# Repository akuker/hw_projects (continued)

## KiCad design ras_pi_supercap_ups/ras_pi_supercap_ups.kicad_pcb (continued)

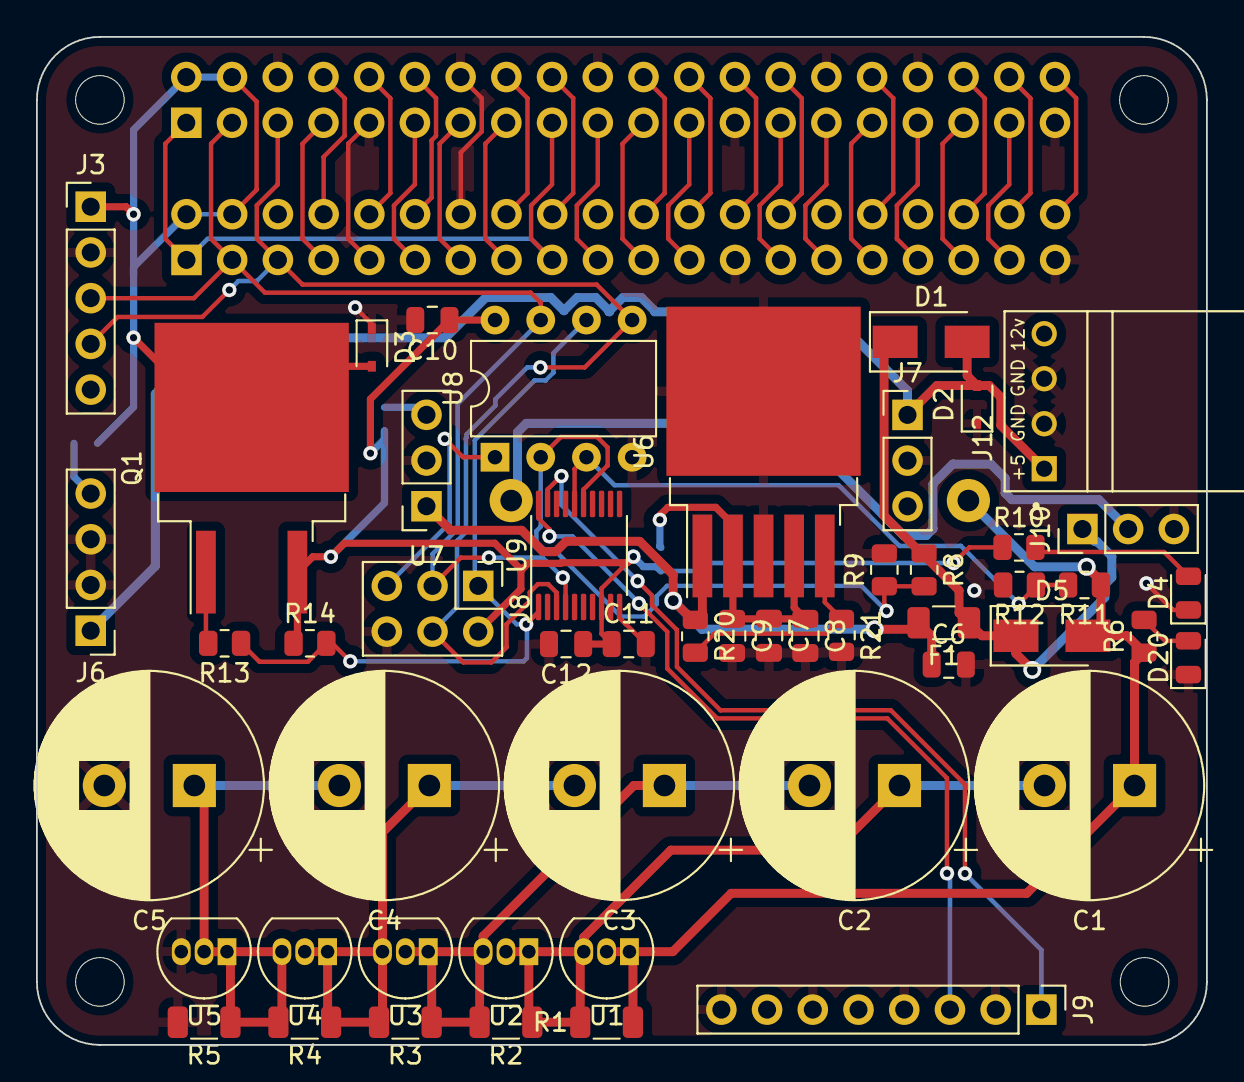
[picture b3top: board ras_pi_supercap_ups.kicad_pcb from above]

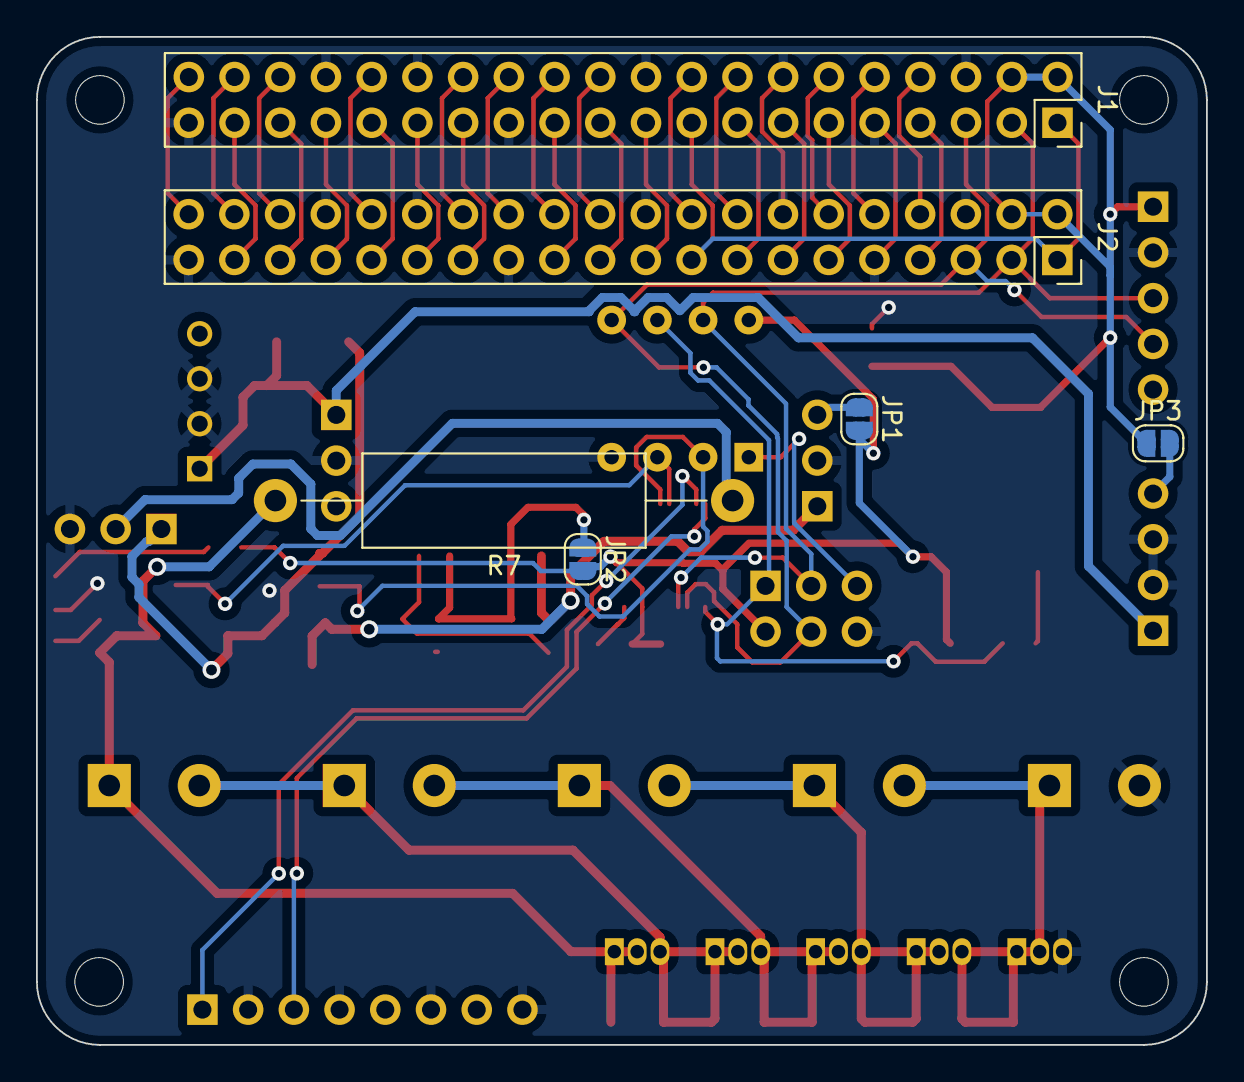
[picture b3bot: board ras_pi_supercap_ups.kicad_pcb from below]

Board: 2 copper layers, 65.0 x 56.0 mm, 61 parts (6 on the bottom side), 54 nets.

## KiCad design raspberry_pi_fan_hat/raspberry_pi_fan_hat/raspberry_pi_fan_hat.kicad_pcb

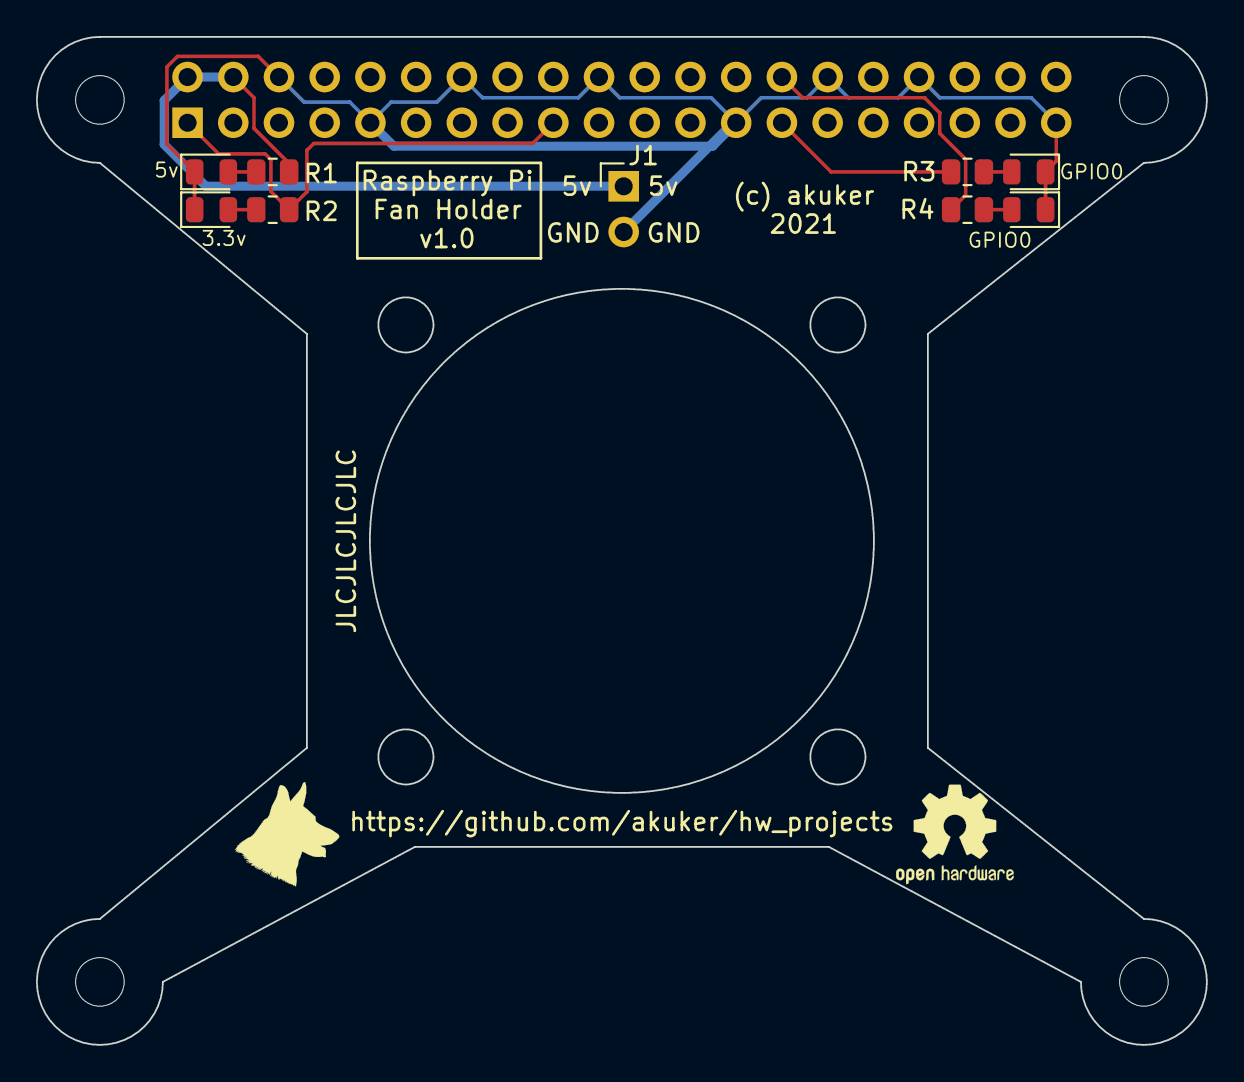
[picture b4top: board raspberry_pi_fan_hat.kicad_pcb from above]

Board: 2 copper layers, 65.0 x 56.0 mm, 14 parts (1 on the bottom side), 9 nets.

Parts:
D1, D2, D3, D4: LED_Small; LED_0805_2012Metric
J1: Conn_01x02; PinHeader_1x02_P2.54mm_Horizontal
MK1, MK2, MK3, MK4: M2.5; MountingHole_2.7mm_M2.5
P1: Conn_02x20_Odd_Even; PinSocket_2x20_P2.54mm_Vertical
R1, R2, R3, R4: R_Small; R_0805_2012Metric

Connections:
+3V3: P1.1, P1.17, R2.1
+5V: J1.1, P1.2, P1.4, R1.1
/ID_SC: P1.28, R4.1
/ID_SD: P1.27, R3.1
GND: D1.1, D2.1, D3.1, D4.1, J1.2, P1.6, P1.9, P1.14, P1.20, P1.25, P1.30, P1.34, P1.39
unnamed: D1.2, R1.2
unnamed: D2.2, R2.2
unnamed: D3.2, R3.2
unnamed: D4.2, R4.2

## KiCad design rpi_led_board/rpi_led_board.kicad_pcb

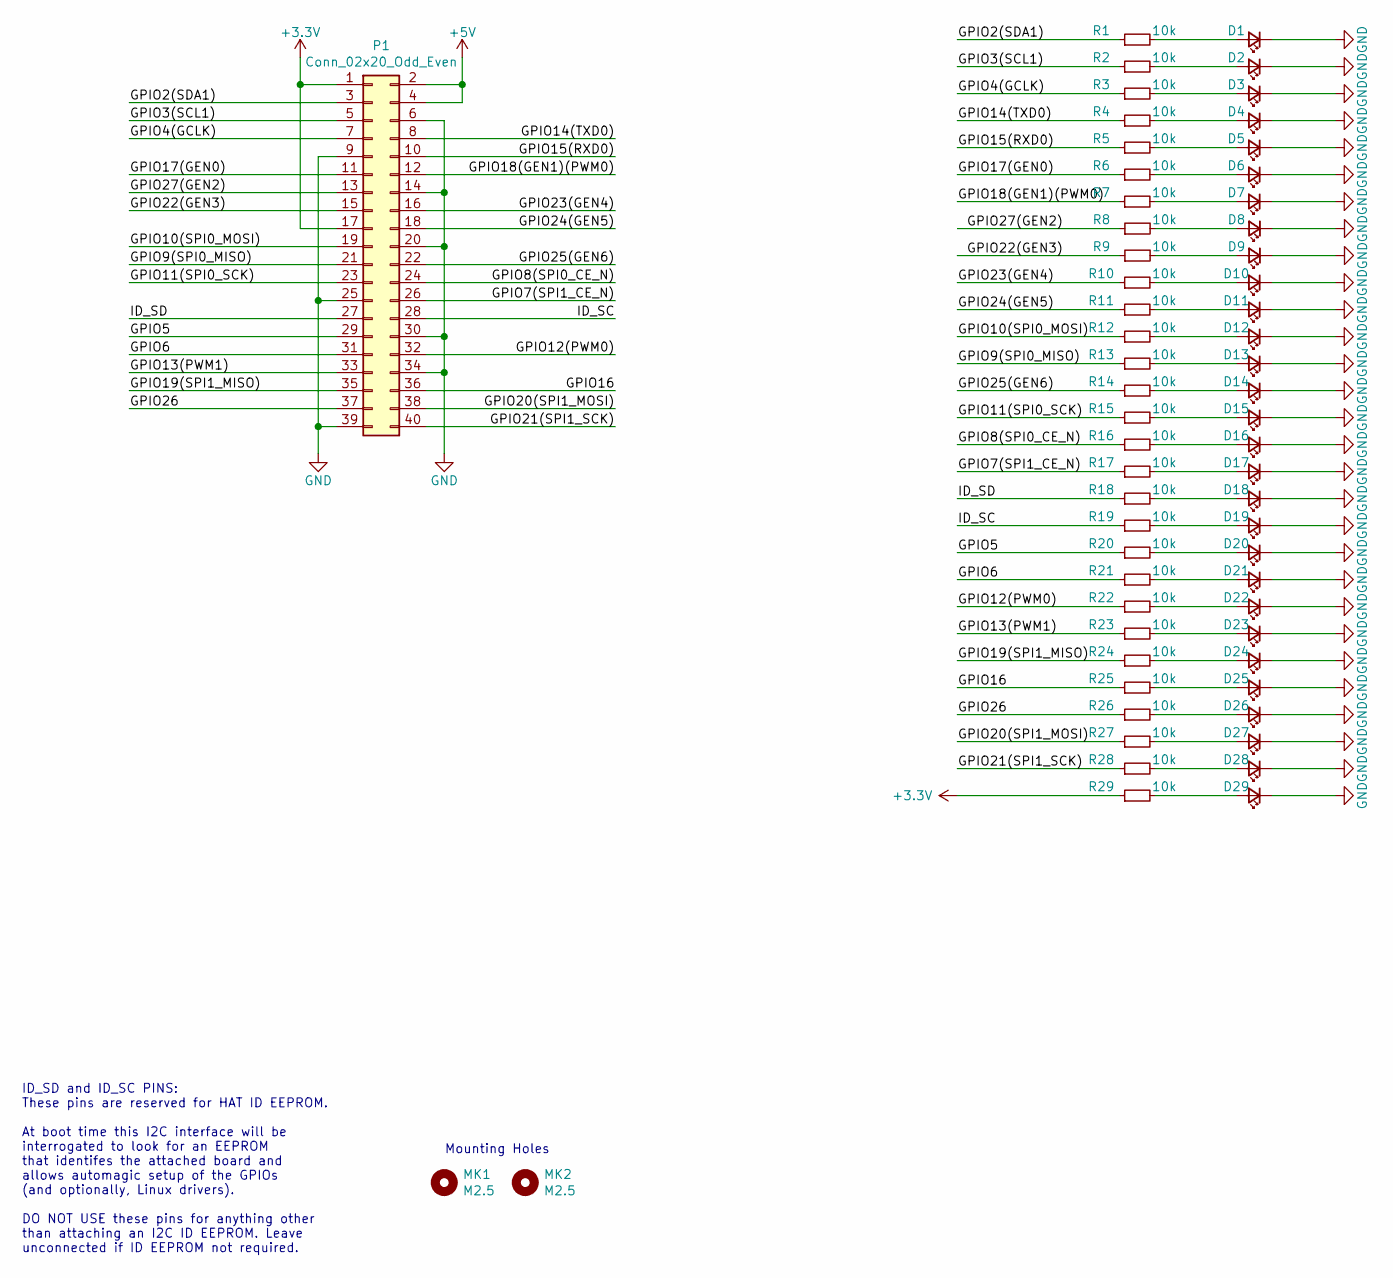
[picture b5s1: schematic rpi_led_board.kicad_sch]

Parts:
D1, D2, D3, D4, D5, D6, D7, D8, D9, D10, D11, D12, D13, D14, D15, D16, D17, D18, D19, D20, D21, D22, D23, D24, D25, D26, D27, D28, D29: Yellow; LED_0805_2012Metric; LCSC C2296
MK1, MK2: M2.5; MountingHole_2.7mm_M2.5
P1: Conn_02x20_Odd_Even; PinSocket_2x20_P2.54mm_Vertical
R1, R2, R3, R4, R5, R6, R7, R8, R9, R10, R11, R12, R13, R14, R15, R16, R17, R18, R19, R20, R21, R22, R23, R24, R25, R26, R27, R28, R29: 10k; R_0805_2012Metric; LCSC C17724

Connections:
+3V3: P1.1, P1.17, R29.1
+5V: P1.2, P1.4
/GPIO2(SDA1): P1.3, R1.1
/GPIO3(SCL1): P1.5, R2.1
/GPIO4(GCLK): P1.7, R3.1
/GPIO5: P1.29, R20.1
/GPIO6: P1.31, R21.1
/GPIO7(SPI1_CE_N): P1.26, R17.1
/GPIO8(SPI0_CE_N): P1.24, R16.1
/GPIO9(SPI0_MISO): P1.21, R13.1
/GPIO10(SPI0_MOSI): P1.19, R12.1
/GPIO11(SPI0_SCK): P1.23, R15.1
/GPIO12(PWM0): P1.32, R22.1
/GPIO13(PWM1): P1.33, R23.1
/GPIO14(TXD0): P1.8, R4.1
/GPIO15(RXD0): P1.10, R5.1
/GPIO16: P1.36, R25.1
/GPIO17(GEN0): P1.11, R6.1
/GPIO18(GEN1)(PWM0): P1.12, R7.1
/GPIO19(SPI1_MISO): P1.35, R24.1
/GPIO20(SPI1_MOSI): P1.38, R27.1
/GPIO21(SPI1_SCK): P1.40, R28.1
/GPIO22(GEN3): P1.15, R9.1
/GPIO23(GEN4): P1.16, R10.1
/GPIO24(GEN5): P1.18, R11.1
/GPIO25(GEN6): P1.22, R14.1
/GPIO26: P1.37, R26.1
/GPIO27(GEN2): P1.13, R8.1
/ID_SC: P1.28, R19.1
/ID_SD: P1.27, R18.1
GND: D1.1 (K), D2.1 (K), D3.1 (K), D4.1 (K), D5.1 (K), D6.1 (K), D7.1 (K), D8.1 (K), D9.1 (K), D10.1 (K), D11.1 (K), D12.1 (K), D13.1 (K), D14.1 (K), D15.1 (K), D16.1 (K), D17.1 (K), D18.1 (K), D19.1 (K), D20.1 (K), D21.1 (K), D22.1 (K), D23.1 (K), D24.1 (K), D25.1 (K), D26.1 (K), D27.1 (K), D28.1 (K), D29.1 (K), P1.6, P1.9, P1.14, P1.20, P1.25, P1.30, P1.34, P1.39
unnamed: D1.2 (A), R1.2
unnamed: D2.2 (A), R2.2
unnamed: D3.2 (A), R3.2
unnamed: D4.2 (A), R4.2
unnamed: D5.2 (A), R5.2
unnamed: D6.2 (A), R6.2
unnamed: D7.2 (A), R7.2
unnamed: D8.2 (A), R8.2
unnamed: D9.2 (A), R9.2
unnamed: D10.2 (A), R10.2
unnamed: D11.2 (A), R11.2
unnamed: D12.2 (A), R12.2
unnamed: D13.2 (A), R13.2
unnamed: D14.2 (A), R14.2
unnamed: D15.2 (A), R15.2
unnamed: D16.2 (A), R16.2
unnamed: D17.2 (A), R17.2
unnamed: D18.2 (A), R18.2
unnamed: D19.2 (A), R19.2
unnamed: D20.2 (A), R20.2
unnamed: D21.2 (A), R21.2
unnamed: D22.2 (A), R22.2
unnamed: D23.2 (A), R23.2
unnamed: D24.2 (A), R24.2
unnamed: D25.2 (A), R25.2
unnamed: D26.2 (A), R26.2
unnamed: D27.2 (A), R27.2
unnamed: D28.2 (A), R28.2
unnamed: D29.2 (A), R29.2

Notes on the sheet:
ID_SD and ID_SC PINS: These pins are reserved for HAT ID EEPROM. At boot time this I2C interface will be interrogated to look for an EEPROM that identifes the attached board and allows automagic setup of the GPIOs (and optionally, Linux drivers). DO NOT USE these pins for anything other than attach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
Mounting Holes

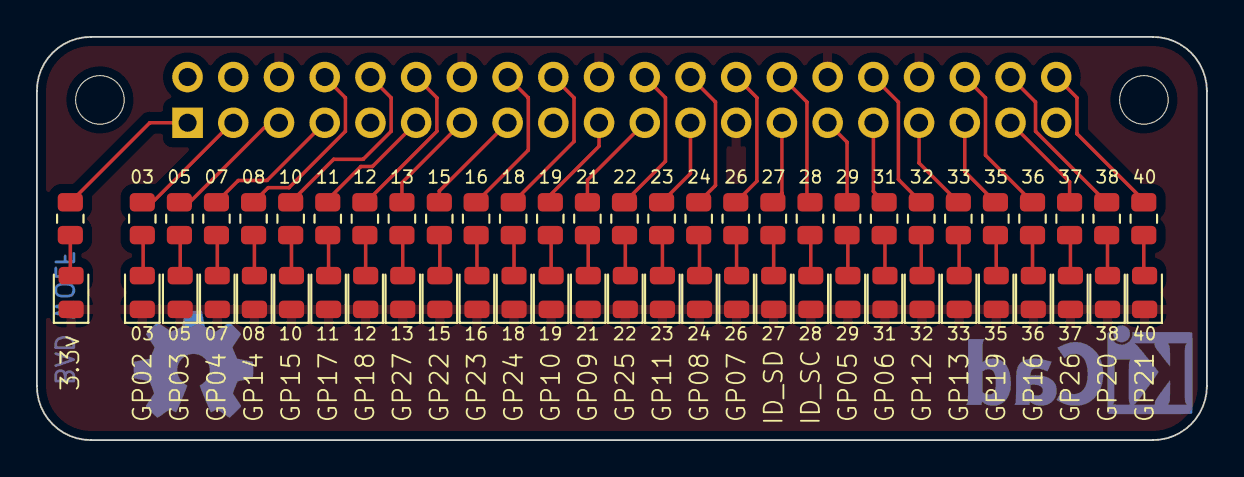
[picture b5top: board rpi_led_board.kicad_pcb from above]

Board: 2 copper layers, 65.0 x 22.4 mm, 61 parts (1 on the bottom side), 60 nets.

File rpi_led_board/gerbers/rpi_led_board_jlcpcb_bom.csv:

Comment,Designator,Footprint,LCSC
"Yellow","D1,D2,D3,D4,D5,D6,D7,D8,D9,D10,D11,D12,D13,D14,D15,D16,D17,D18,D19,D20,D21,D22,D23,D24,D25,D26,D27,D28,D29","LED_SMD:LED_0805_2012Metric","C2296"
"M2.5","MK1,MK2","MountingHole:MountingHole_2.7mm_M2.5",""
"Conn_02x20_Odd_Even","P1","Connector_PinSocket_2.54mm:PinSocket_2x20_P2.54mm_Vertical",""
"10k","R1,R2,R3,R4,R5,R6,R7,R8,R9,R10,R11,R12,R13,R14,R15,R16,R17,R18,R19,R20,R21,R22,R23,R24,R25,R26,R27,R28,R29","Resistor_SMD:R_0805_2012Metric","C17724"

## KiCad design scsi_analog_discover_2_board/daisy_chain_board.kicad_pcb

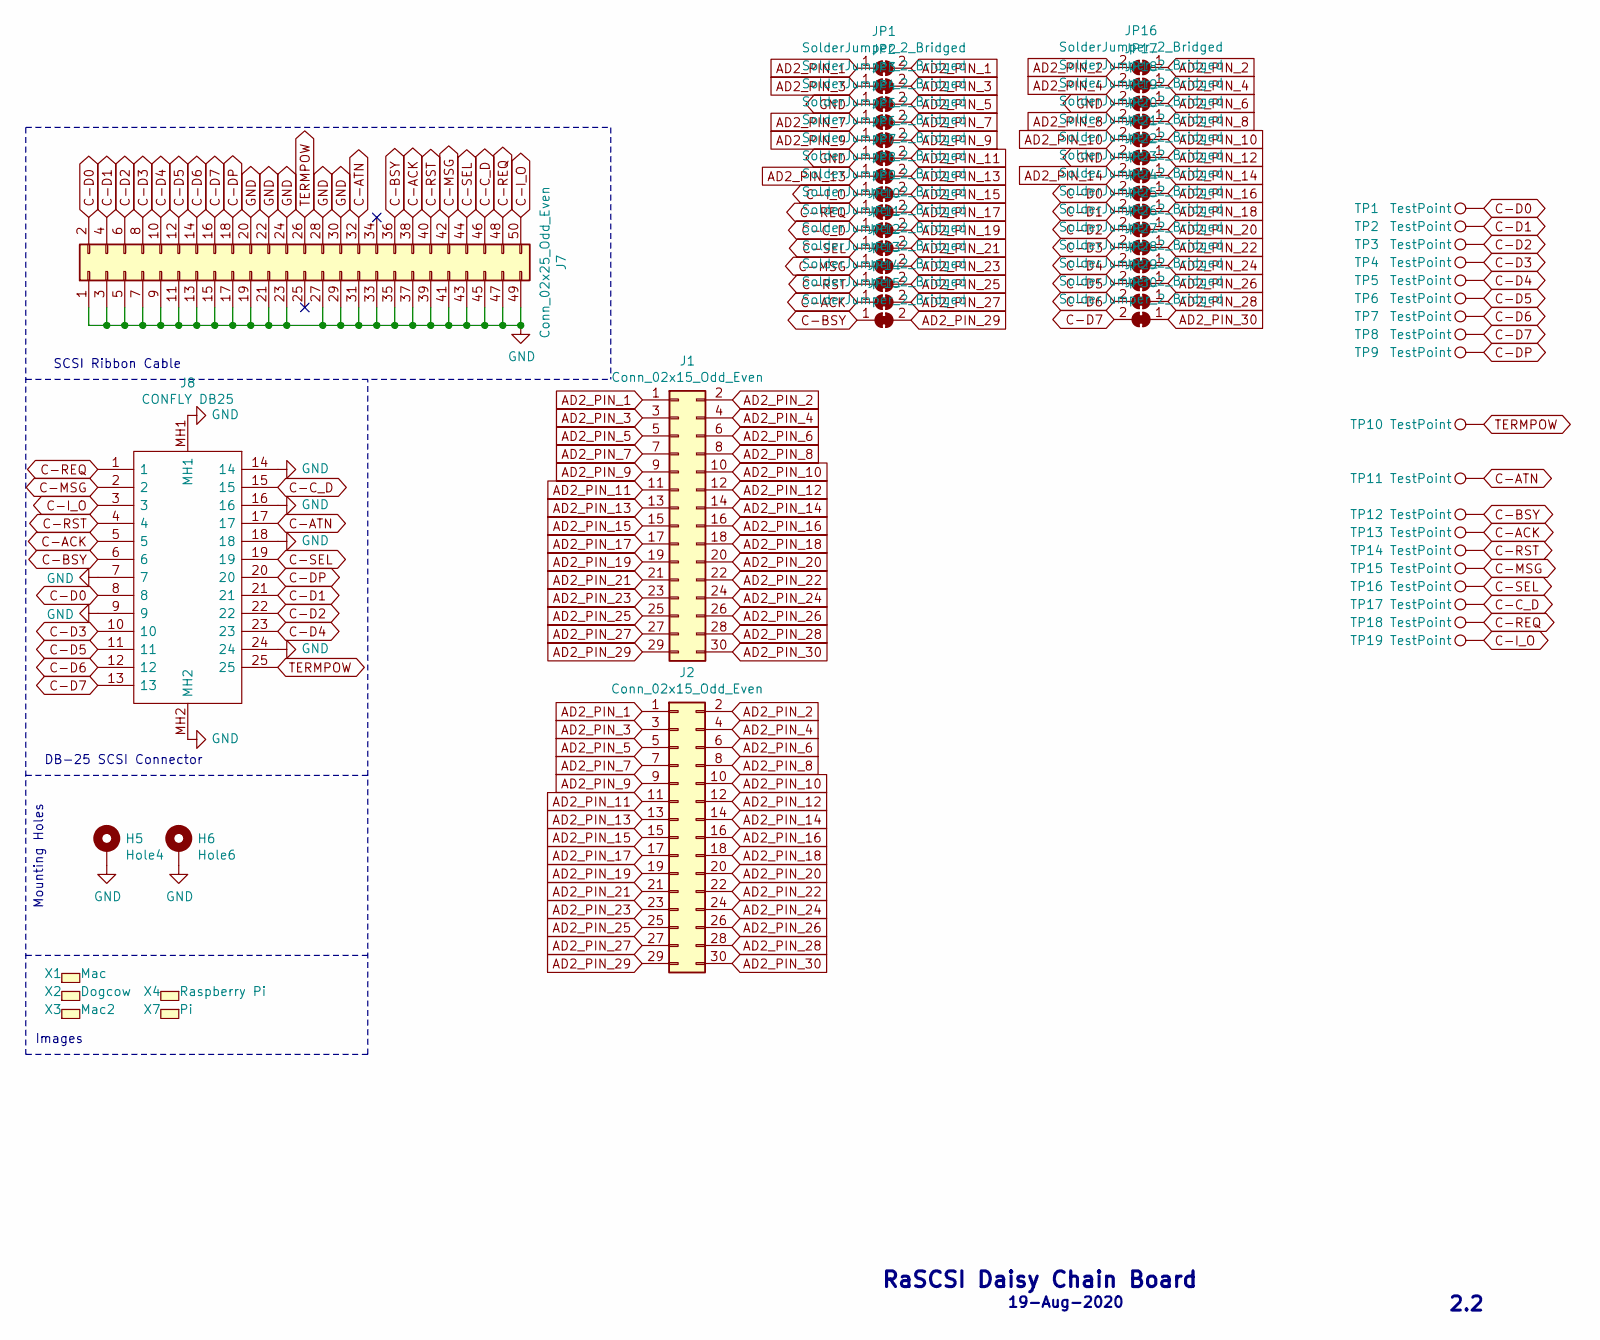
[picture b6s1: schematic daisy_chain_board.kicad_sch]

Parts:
H5: Hole4; MountingHole_2.7mm_M2.5_Pad_Via
H6: Hole6; MountingHole_2.7mm_M2.5_Pad_Via
J1, J2: Conn_02x15_Odd_Even; PinHeader_2x15_P2.54mm_Vertical
J7: Conn_02x25_Odd_Even; PinSocket_2x25_P2.54mm_Vertical; LCSC C40024
J8: CONFLY DB25; 57489011; Mouser Part Number 523-L717SDB25PA4CH4F
JP1, JP2, JP3, JP4, JP5, JP6, JP7, JP8, JP9, JP10, JP11, JP12, JP13, JP14, JP15, JP16, JP17, JP18, JP19, JP20, JP21, JP22, JP23, JP24, JP25, JP26, JP27, JP28, JP29, JP30: SolderJumper_2_Bridged; SolderJumper-2_P1.3mm_Bridged_RoundedPad1.0x1.5mm
TP1, TP2, TP3, TP4, TP5, TP6, TP7, TP8, TP9, TP10, TP11, TP12, TP13, TP14, TP15, TP16, TP17, TP18, TP19: TestPoint; TestPoint_Loop_D2.50mm_Drill1.0mm
X1: Mac; mac_happy_small
X2: Dogcow; dogcow
X3: Mac2; mac_happy_small
X4: Raspberry Pi; pi_logo
X7: Pi; pi_logo

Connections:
AD2_PIN_1: J1.1, J2.1, JP1.1 (A), JP1.2 (B)
AD2_PIN_2: J1.2, J2.2, JP16.1 (A), JP16.2 (B)
AD2_PIN_3: J1.3, J2.3, JP2.1 (A), JP2.2 (B)
AD2_PIN_4: J1.4, J2.4, JP17.1 (A), JP17.2 (B)
AD2_PIN_5: J1.5, J2.5, JP3.2 (B)
AD2_PIN_6: J1.6, J2.6, JP18.1 (A)
AD2_PIN_7: J1.7, J2.7, JP4.1 (A), JP4.2 (B)
AD2_PIN_8: J1.8, J2.8, JP19.1 (A), JP19.2 (B)
AD2_PIN_9: J1.9, J2.9, JP5.1 (A), JP5.2 (B)
AD2_PIN_10: J1.10, J2.10, JP20.1 (A), JP20.2 (B)
AD2_PIN_11: J1.11, J2.11, JP6.2 (B)
AD2_PIN_12: J1.12, J2.12, JP21.1 (A)
AD2_PIN_13: J1.13, J2.13, JP7.1 (A), JP7.2 (B)
AD2_PIN_14: J1.14, J2.14, JP22.1 (A), JP22.2 (B)
AD2_PIN_15: J1.15, J2.15, JP8.2 (B)
AD2_PIN_16: J1.16, J2.16, JP23.1 (A)
AD2_PIN_17: J1.17, J2.17, JP9.2 (B)
AD2_PIN_18: J1.18, J2.18, JP24.1 (A)
AD2_PIN_19: J1.19, J2.19, JP10.2 (B)
AD2_PIN_20: J1.20, J2.20, JP25.1 (A)
AD2_PIN_21: J1.21, J2.21, JP11.2 (B)
AD2_PIN_22: J1.22, J2.22, JP26.1 (A)
AD2_PIN_23: J1.23, J2.23, JP12.2 (B)
AD2_PIN_24: J1.24, J2.24, JP27.1 (A)
AD2_PIN_25: J1.25, J2.25, JP13.2 (B)
AD2_PIN_26: J1.26, J2.26, JP28.1 (A)
AD2_PIN_27: J1.27, J2.27, JP14.2 (B)
AD2_PIN_28: J1.28, J2.28, JP29.1 (A)
AD2_PIN_29: J1.29, J2.29, JP15.2 (B)
AD2_PIN_30: J1.30, J2.30, JP30.1 (A)
C-ACK: J7.38, J8.5, JP14.1 (A), TP13.1
C-ATN: J7.32, J8.17, TP11.1
C-BSY: J7.36, J8.6, JP15.1 (A), TP12.1
C-C_D: J7.46, J8.15, JP10.1 (A), TP17.1
C-D0: J7.2, J8.8, JP23.2 (B), TP1.1
C-D1: J7.4, J8.21, JP24.2 (B), TP2.1
C-D2: J7.6, J8.22, JP25.2 (B), TP3.1
C-D3: J7.8, J8.10, JP26.2 (B), TP4.1
C-D4: J7.10, J8.23, JP27.2 (B), TP5.1
C-D5: J7.12, J8.11, JP28.2 (B), TP6.1
C-D6: J7.14, J8.12, JP29.2 (B), TP7.1
C-D7: J7.16, J8.13, JP30.2 (B), TP8.1
C-DP: J7.18, J8.20, TP9.1
C-I_O: J7.50, J8.3, JP8.1 (A), TP19.1
C-MSG: J7.42, J8.2, JP12.1 (A), TP15.1
C-REQ: J7.48, J8.1, JP9.1 (A), TP18.1
C-RST: J7.40, J8.4, JP13.1 (A), TP14.1
C-SEL: J7.44, J8.19, JP11.1 (A), TP16.1
GND: H5.1, H6.1, J7.1, J7.3, J7.5, J7.7, J7.9, J7.11, J7.13, J7.15, J7.17, J7.19, J7.20, J7.21, J7.22, J7.23, J7.24, J7.27, J7.28, J7.29, J7.30, J7.31, J7.33, J7.35, J7.37, J7.39, J7.41, J7.43, J7.45, J7.47, J7.49, J8.7, J8.9, J8.14, J8.16, J8.18, J8.24, J8.MH1, J8.MH2, JP3.1 (A), JP6.1 (A), JP18.2 (B), JP21.2 (B)
TERMPOW: J7.26, J8.25, TP10.1

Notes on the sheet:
Images
DB-25 SCSI Connector
Mounting Holes
SCSI Ribbon Cable
RaSCSI Daisy Chain Board
19-Aug-2020
2.2

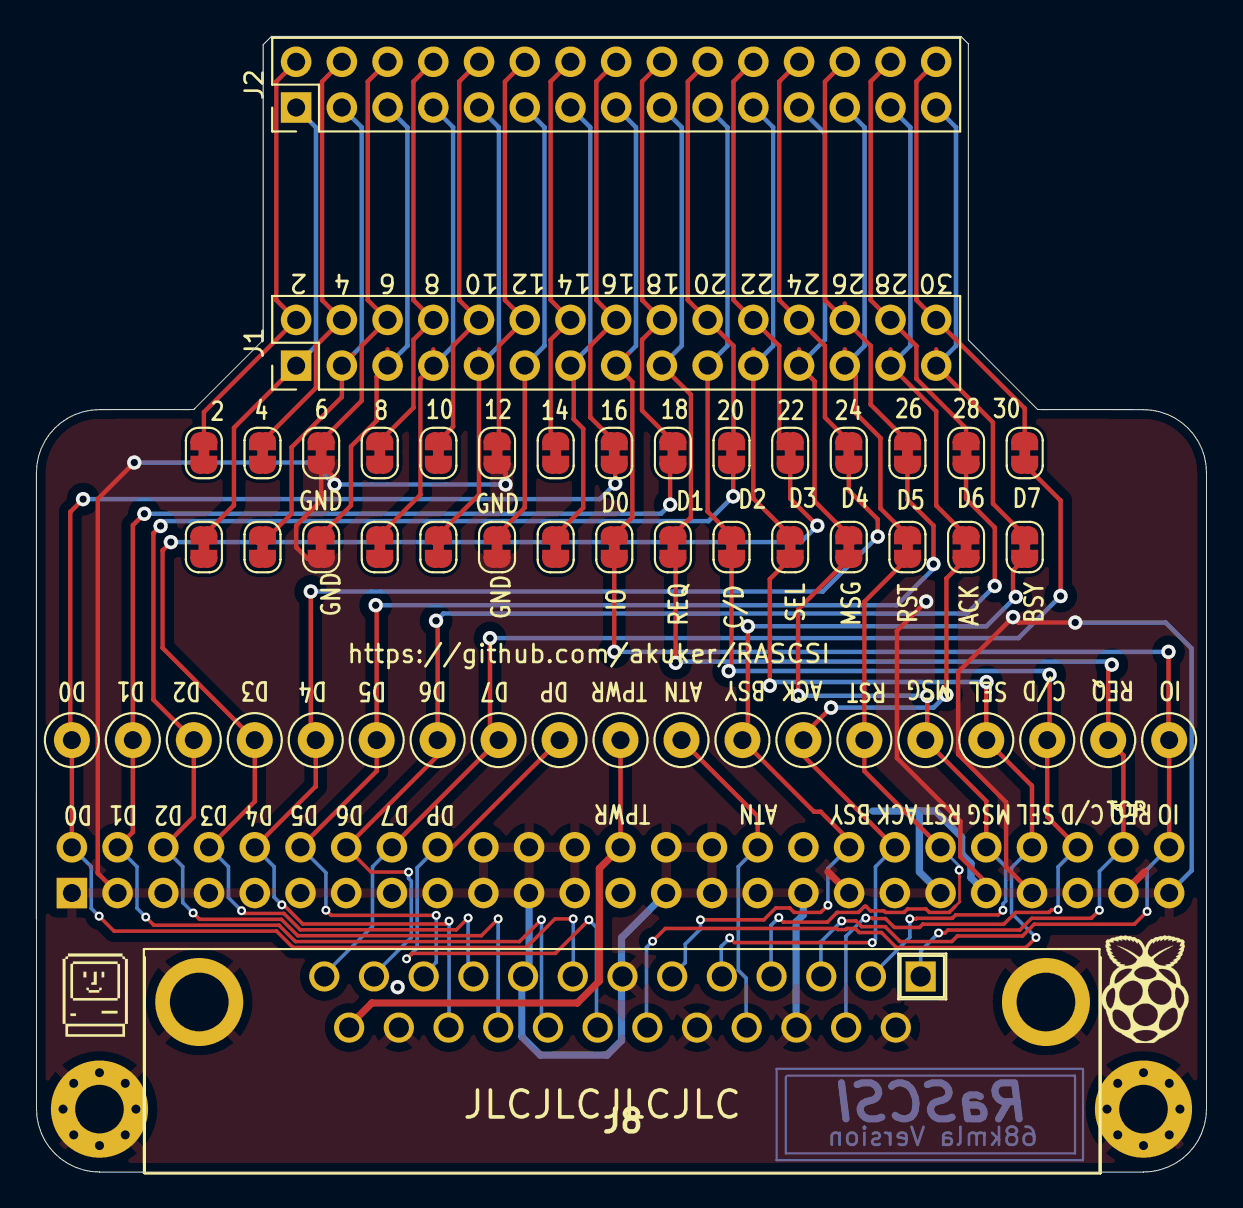
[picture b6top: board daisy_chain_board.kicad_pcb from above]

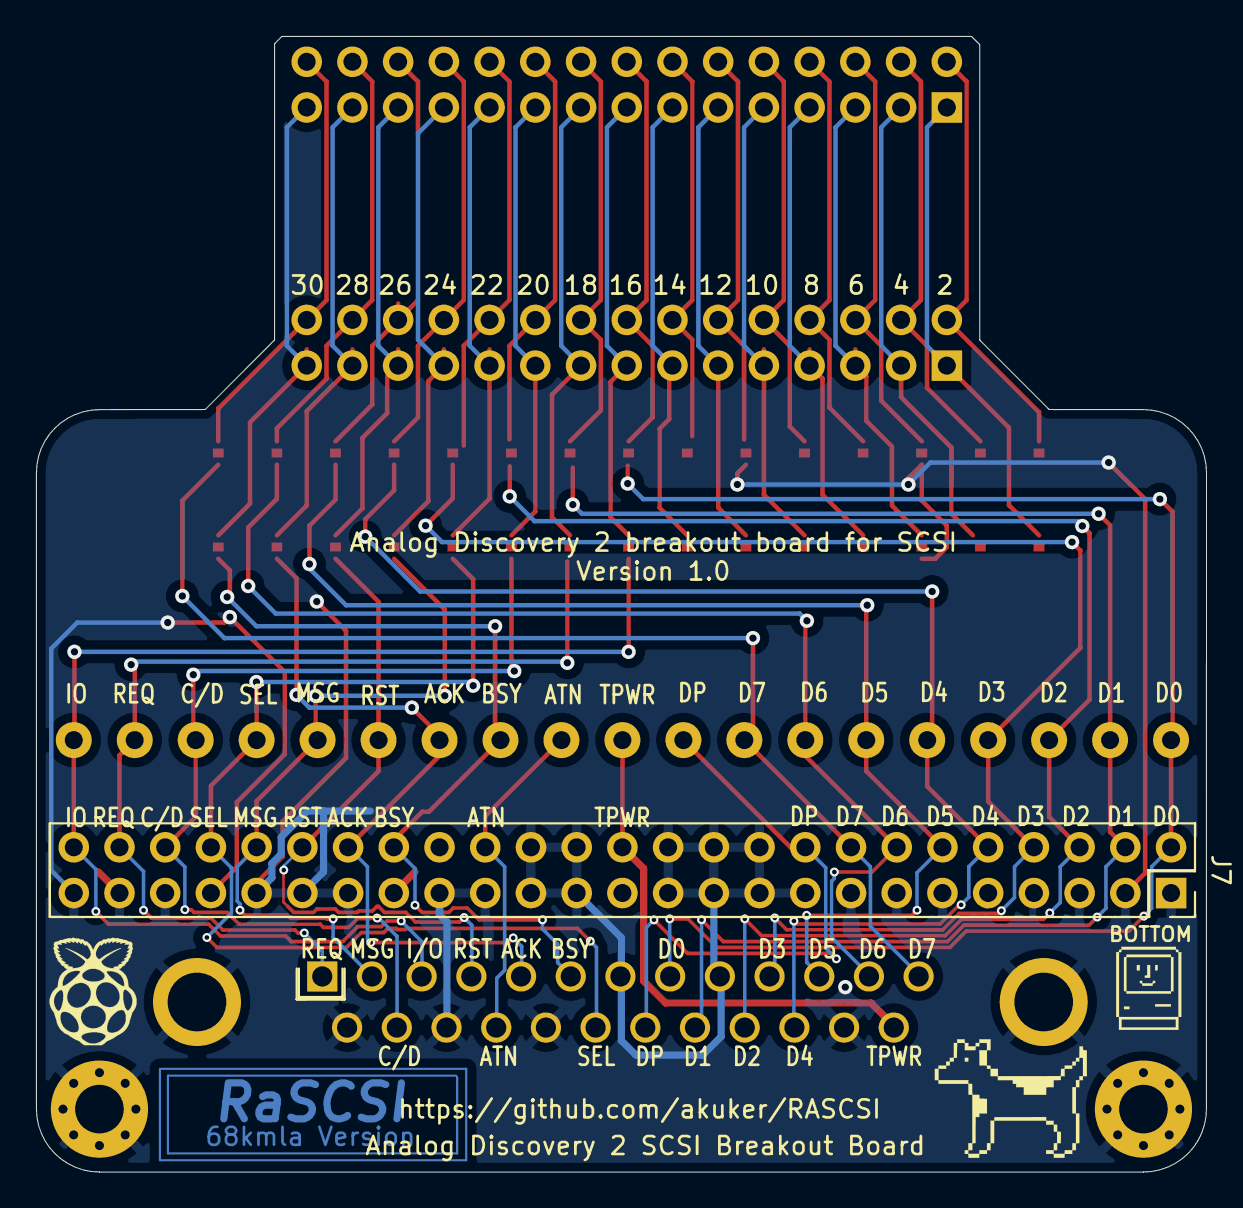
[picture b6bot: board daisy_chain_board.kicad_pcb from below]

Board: 2 copper layers, 65.0 x 63.1 mm, 60 parts (4 on the bottom side), 50 nets.

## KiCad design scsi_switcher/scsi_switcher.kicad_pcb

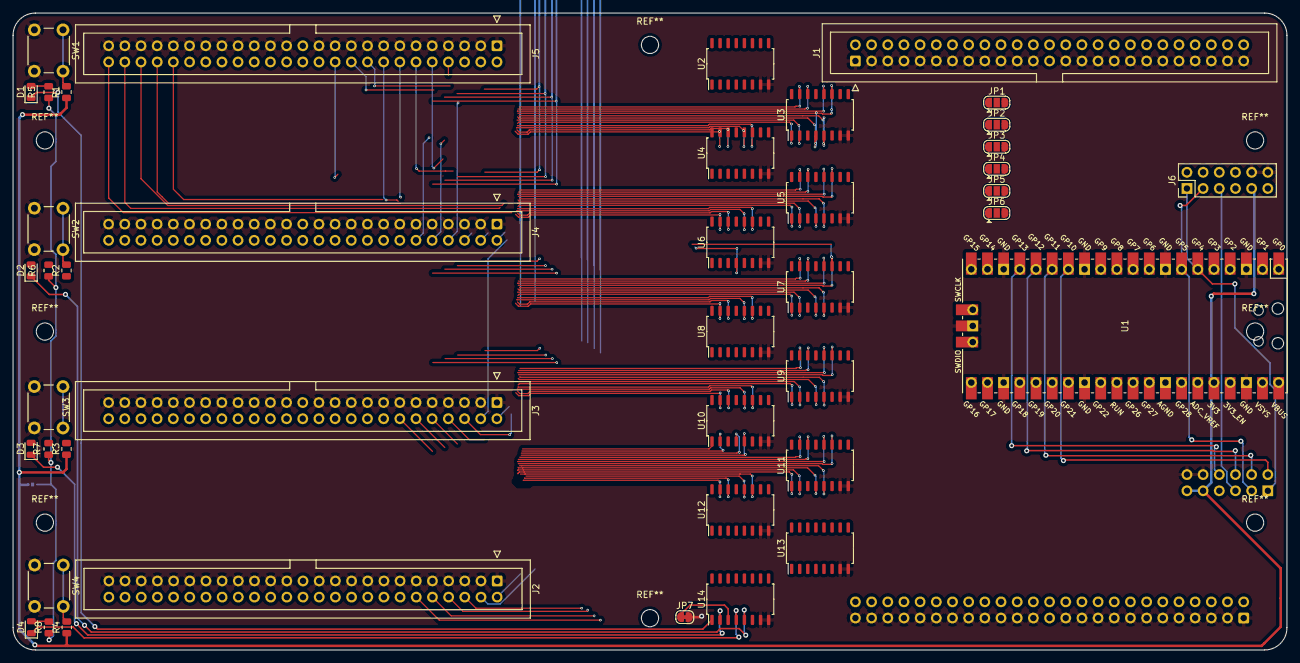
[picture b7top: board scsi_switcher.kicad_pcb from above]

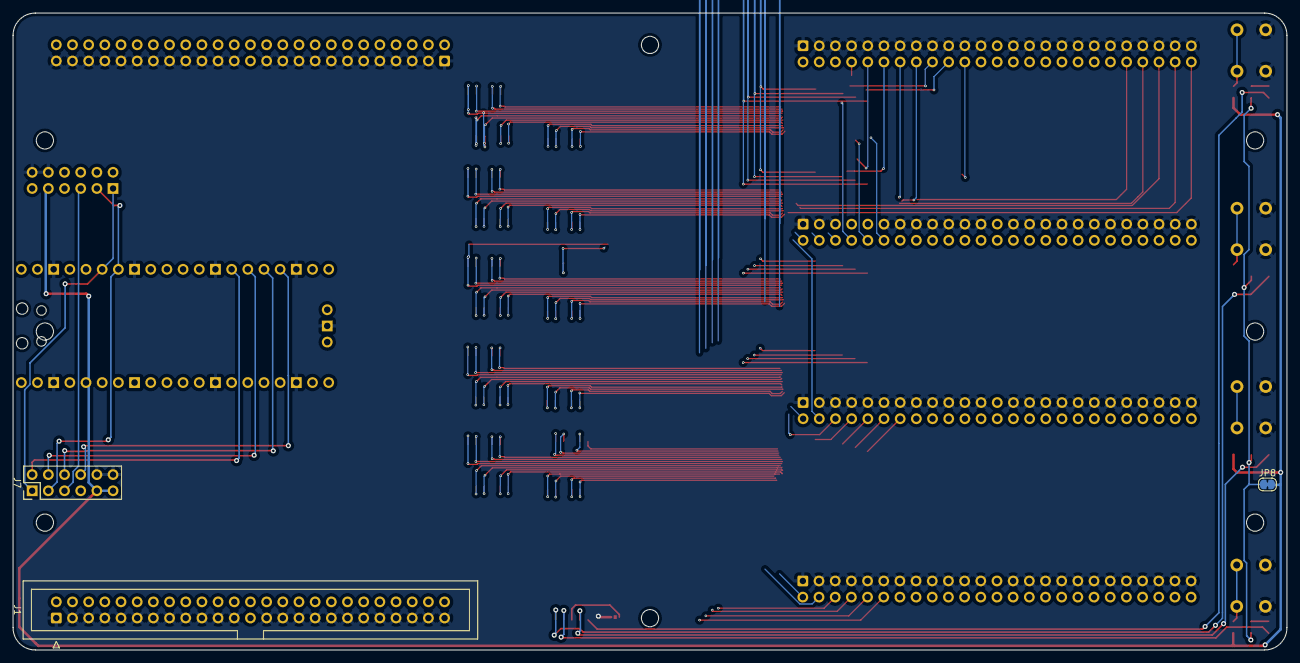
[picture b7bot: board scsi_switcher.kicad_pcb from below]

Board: 2 copper layers, 200.0 x 100.0 mm, 46 parts (3 on the bottom side), 156 nets.

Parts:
D1: SEL 0; LED_0805_2012Metric
D2: SEL 1; LED_0805_2012Metric
D3: SEL 2; LED_0805_2012Metric
D4: SEL 3; LED_0805_2012Metric
J1, J1#2, J2, J3, J4, J5: Conn_02x25_Counter_Clockwise; IDC-Header_2x25_P2.54mm_Vertical
J6, J7: Conn_02x06_Odd_Even; PinHeader_2x06_P2.54mm_Vertical
JP1, JP2, JP3, JP4, JP5, JP6: SolderJumper_3_Open; SolderJumper-3_P1.3mm_Open_RoundedPad1.0x1.5mm
JP7, JP8: SolderJumper_2_Bridged; SolderJumper-2_P1.3mm_Bridged_RoundedPad1.0x1.5mm
R1, R2, R3, R4, R5, R6, R7, R8: R_Small; R_0805_2012Metric
SW1: SELECT 0; SW_PUSH_6mm
SW2: SELECT 1; SW_PUSH_6mm
SW3: SELECT 2; SW_PUSH_6mm
SW4: SELECT 3; SW_PUSH_6mm
U1: Pico; RPi_Pico_SMD_TH
U2, U3, U4, U5, U6, U7, U8, U9, U10, U11, U12, U13, U14: CD4052B; SOIC-16_4.55x10.3mm_P1.27mm

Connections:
+3V3: J6.9, J6.11, J7.9, J7.11, JP8.2 (B), R1.1, R2.1, R3.1, R4.1, U1.36 (3V3), U2.16 (VDD), U3.16 (VDD), U4.16 (VDD), U5.16 (VDD), U6.16 (VDD), U7.16 (VDD), U8.16 (VDD), U9.16 (VDD), U10.16 (VDD), U11.16 (VDD), U12.16 (VDD), U13.16 (VDD), U14.16 (VDD)
BUTTON_SELECT_0: JP1.2 (C), R1.2, SW1.1
BUTTON_SELECT_1: JP2.2 (C), R2.2, SW2.1
BUTTON_SELECT_2: JP3.2 (C), R3.2, SW3.1
BUTTON_SELECT_3: JP4.2 (C), R4.2, SW4.1
GND: J1.1, J1.3, J1.5, J1.7, J1.9, J1.11, J1.13, J1.15, J1.17, J1.19, J1.21, J1.23, J1.27, J1.29, J1.31, J1.33, J1.35, J1.37, J1.39, J1.41, J1.43, J1.45, J1.47, J1.49, J1#2.1, J1#2.3, J1#2.5, J1#2.7, J1#2.9, J1#2.11, J1#2.13, J1#2.15, J1#2.17, J1#2.19, J1#2.21, J1#2.23, J1#2.27, J1#2.29, J1#2.31, J1#2.33, J1#2.35, J1#2.37, J1#2.39, J1#2.41, J1#2.43, J1#2.45, J1#2.47, J1#2.49, J2.1, J2.3, J2.5, J2.7, J2.9, J2.11, J2.13, J2.15, J2.17, J2.19, J2.21, J2.23, J2.27, J2.29, J2.31, J2.33, J2.35, J2.37, J2.39, J2.41, J2.43, J2.45, J2.47, J2.49, J3.1, J3.3, J3.5, J3.7, J3.9, J3.11, J3.13, J3.15, J3.17, J3.19, J3.21, J3.23, J3.27, J3.29, J3.31, J3.33, J3.35, J3.37, J3.39, J3.41, J3.43, J3.45, J3.47, J3.49, J4.1, J4.3, J4.5, J4.7, J4.9, J4.11, J4.13, J4.15, J4.17, J4.19, J4.21, J4.23, J4.27, J4.29, J4.31, J4.33, J4.35, J4.37, J4.39, J4.41, J4.43, J4.45, J4.47, J4.49, J5.1, J5.3, J5.5, J5.7, J5.9, J5.11, J5.13, J5.15, J5.17, J5.19, J5.21, J5.23, J5.27, J5.29, J5.31, J5.33, J5.35, J5.37, J5.39, J5.41, J5.43, J5.45, J5.47, J5.49, J6.10, J6.12, J7.10, J7.12, JP7.2 (B), SW1.2, SW2.2, SW3.2, SW4.2, U1.3 (GND), U1.8 (GND), U1.13 (GND), U1.18 (GND), U1.23 (GND), U1.28 (GND), U1.38 (GND), U1.42 (GND), U2.7 (VEE), U2.8 (VSS), U3.7 (VEE), U3.8 (VSS), U4.7 (VEE), U4.8 (VSS), U5.7 (VEE), U5.8 (VSS), U6.7 (VEE), U6.8 (VSS), U7.7 (VEE), U7.8 (VSS), U8.7 (VEE), U8.8 (VSS), U9.7 (VEE), U9.8 (VSS), U10.7 (VEE), U10.8 (VSS), U11.7 (VEE), U11.8 (VSS), U12.7 (VEE), U12.8 (VSS), U13.7 (VEE), U13.8 (VSS), U14.7 (VEE), U14.8 (VSS)
GPIO_BUTTON_SELECT_0: JP1.3 (B), U1.9 (GPIO6)
GPIO_BUTTON_SELECT_1: JP2.3 (B), U1.10 (GPIO7)
GPIO_BUTTON_SELECT_2: JP3.3 (B), U1.11 (GPIO8)
GPIO_BUTTON_SELECT_3: JP4.3 (B), U1.12 (GPIO9)
GPIO_BUTTON_SELECT_4: J6.2, J7.2, JP1.1 (A), U1.14 (GPIO10)
GPIO_BUTTON_SELECT_5: J6.4, J7.4, JP2.1 (A), U1.15 (GPIO11)
GPIO_BUTTON_SELECT_6: J6.6, J7.6, JP3.1 (A), U1.16 (GPIO12)
GPIO_BUTTON_SELECT_7: J6.8, J7.8, JP4.1 (A), U1.17 (GPIO13)
GPIO_MUX_SELECT_A: JP5.3 (B), U1.4 (GPIO2)
GPIO_MUX_SELECT_B: JP6.3 (B), U1.5 (GPIO3)
GPIO_MUX_SELECT_C: J6.1, J7.1, JP5.1 (A), U1.6 (GPIO4)
GPIO_MUX_SELECT_D: J6.3, J7.3, JP6.1 (A), U1.7 (GPIO5)
J1_Pin2: J1.2, J1#2.2, U2.13 (X)
J1_Pin4: J1.4, J1#2.4, U2.3 (Y)
J1_Pin6: J1.6, J1#2.6, U3.13 (X)
J1_Pin8: J1.8, J1#2.8, U3.3 (Y)
J1_Pin10: J1.10, J1#2.10, U4.13 (X)
J1_Pin12: J1.12, J1#2.12, U4.3 (Y)
J1_Pin14: J1.14, J1#2.14, U5.13 (X)
J1_Pin16: J1.16, J1#2.16, U5.3 (Y)
J1_Pin18: J1.18, J1#2.18, U6.13 (X)
J1_Pin20: J1.20, J1#2.20, U6.3 (Y)
J1_Pin22: J1.22, J1#2.22, U7.13 (X)
J1_Pin24: J1.24, J1#2.24, U7.3 (Y)
J1_Pin26: J1.26, J1#2.26, U8.13 (X)
J1_Pin28: J1.28, J1#2.28, U8.3 (Y)
J1_Pin30: J1.30, J1#2.30, U9.13 (X)
J1_Pin32: J1.32, J1#2.32, U9.3 (Y)
J1_Pin34: J1.34, J1#2.34, U10.13 (X)
J1_Pin36: J1.36, J1#2.36, U10.3 (Y)
J1_Pin38: J1.38, J1#2.38, U11.13 (X)
J1_Pin40: J1.40, J1#2.40, U11.3 (Y)
J1_Pin42: J1.42, J1#2.42, U12.13 (X)
J1_Pin44: J1.44, J1#2.44, U12.3 (Y)
J1_Pin46: J1.46, J1#2.46, U13.13 (X)
J1_Pin48: J1.48, J1#2.48, U13.3 (Y)
J1_Pin50: J1.50, J1#2.50, U14.13 (X)
J2_Pin2: J2.2, U2.12 (X0)
J2_Pin4: J2.4, U2.1 (Y0)
J2_Pin6: J2.6, U3.12 (X0)
J2_Pin8: J2.8, U3.1 (Y0)
J2_Pin10: J2.10, U4.12 (X0)
J2_Pin12: J2.12, U4.1 (Y0)
J2_Pin14: J2.14, U5.12 (X0)
J2_Pin16: J2.16, U5.1 (Y0)
J2_Pin18: J2.18, U6.12 (X0)
J2_Pin20: J2.20, U6.1 (Y0)
J2_Pin22: J2.22, U7.12 (X0)
J2_Pin24: J2.24, U7.1 (Y0)
J2_Pin26: J2.26, U8.12 (X0)
J2_Pin28: J2.28, U8.1 (Y0)
J2_Pin30: J2.30, U9.12 (X0)
J2_Pin32: J2.32, U9.1 (Y0)
J2_Pin34: J2.34, U10.12 (X0)
J2_Pin36: J2.36, U10.1 (Y0)
J2_Pin38: J2.38, U11.12 (X0)
J2_Pin40: J2.40, U11.1 (Y0)
J2_Pin42: J2.42, U12.12 (X0)
J2_Pin44: J2.44, U12.1 (Y0)
J2_Pin46: J2.46, U13.12 (X0)
J2_Pin48: J2.48, U13.1 (Y0)
J2_Pin50: J2.50, U14.12 (X0)
J3_Pin2: J3.2, U2.14 (X1)
J3_Pin4: J3.4, U2.5 (Y1)
J3_Pin6: J3.6, U3.14 (X1)
J3_Pin8: J3.8, U3.5 (Y1)
J3_Pin10: J3.10, U4.14 (X1)
J3_Pin12: J3.12, U4.5 (Y1)
J3_Pin14: J3.14, U5.14 (X1)
J3_Pin16: J3.16, U5.5 (Y1)
J3_Pin18: J3.18, U6.14 (X1)
J3_Pin20: J3.20, U6.5 (Y1)
J3_Pin22: J3.22, U7.14 (X1)
J3_Pin24: J3.24, U7.5 (Y1)
J3_Pin26: J3.26, U8.14 (X1)
J3_Pin28: J3.28, U8.5 (Y1)
J3_Pin30: J3.30, U9.14 (X1)
J3_Pin32: J3.32, U9.5 (Y1)
J3_Pin34: J3.34, U10.14 (X1)
J3_Pin36: J3.36, U10.5 (Y1)
J3_Pin38: J3.38, U11.14 (X1)
J3_Pin40: J3.40, U11.5 (Y1)
J3_Pin42: J3.42, U12.14 (X1)
J3_Pin44: J3.44, U12.5 (Y1)
J3_Pin46: J3.46, U13.14 (X1)
J3_Pin48: J3.48, U13.5 (Y1)
J3_Pin50: J3.50, U14.14 (X1)
J4_Pin2: J4.2, U2.15 (X2)
J4_Pin4: J4.4, U2.2 (Y2)
J4_Pin6: J4.6, U3.15 (X2)
J4_Pin8: J4.8, U3.2 (Y2)
J4_Pin10: J4.10, U4.15 (X2)
J4_Pin12: J4.12, U4.2 (Y2)
J4_Pin14: J4.14, U5.15 (X2)
J4_Pin16: J4.16, U5.2 (Y2)
J4_Pin18: J4.18, U6.15 (X2)
J4_Pin20: J4.20, U6.2 (Y2)
J4_Pin22: J4.22, U7.15 (X2)
J4_Pin24: J4.24, U7.2 (Y2)
J4_Pin26: J4.26, U8.15 (X2)
J4_Pin28: J4.28, U8.2 (Y2)
J4_Pin30: J4.30, U9.15 (X2)
J4_Pin32: J4.32, U9.2 (Y2)
J4_Pin34: J4.34, U10.15 (X2)
J4_Pin36: J4.36, U10.2 (Y2)
J4_Pin38: J4.38, U11.15 (X2)
J4_Pin40: J4.40, U11.2 (Y2)
J4_Pin42: J4.42, U12.15 (X2)
J4_Pin44: J4.44, U12.2 (Y2)
J4_Pin46: J4.46, U13.15 (X2)
J4_Pin48: J4.48, U13.2 (Y2)
J4_Pin50: J4.50, U14.15 (X2)
J5_Pin2: J5.2, U2.11 (X3)
J5_Pin4: J5.4, U2.4 (Y3)
J5_Pin6: J5.6, U3.11 (X3)
J5_Pin8: J5.8, U3.4 (Y3)
J5_Pin10: J5.10, U4.11 (X3)
J5_Pin12: J5.12, U4.4 (Y3)
J5_Pin14: J5.14, U5.11 (X3)
J5_Pin16: J5.16, U5.4 (Y3)
J5_Pin18: J5.18, U6.11 (X3)
J5_Pin20: J5.20, U6.4 (Y3)
J5_Pin22: J5.22, U7.11 (X3)
J5_Pin24: J5.24, U7.4 (Y3)
J5_Pin26: J5.26, U8.11 (X3)
J5_Pin28: J5.28, U8.4 (Y3)
J5_Pin30: J5.30, U9.11 (X3)
J5_Pin32: J5.32, U9.4 (Y3)
J5_Pin34: J5.34, U10.11 (X3)
J5_Pin36: J5.36, U10.4 (Y3)
J5_Pin38: J5.38, U11.11 (X3)
J5_Pin40: J5.40, U11.4 (Y3)
J5_Pin42: J5.42, U12.11 (X3)
J5_Pin44: J5.44, U12.4 (Y3)
J5_Pin46: J5.46, U13.11 (X3)
J5_Pin48: J5.48, U13.4 (Y3)
J5_Pin50: J5.50, U14.11 (X3)
MUX_INHIBIT: J6.5, J7.5, U1.19 (GPIO14), U2.6 (INH), U3.6 (INH), U4.6 (INH), U5.6 (INH), U6.6 (INH), U7.6 (INH), U8.6 (INH), U9.6 (INH), U10.6 (INH), U11.6 (INH), U12.6 (INH), U13.6 (INH), U14.6 (INH)
MUX_SELECT_A: JP5.2 (C), U2.10 (A), U3.10 (A), U4.10 (A), U5.10 (A), U6.10 (A), U7.10 (A), U8.10 (A), U9.10 (A), U10.10 (A), U11.10 (A), U12.10 (A), U13.10 (A), U14.10 (A)
MUX_SELECT_B: JP6.2 (C), U2.9 (B), U3.9 (B), U4.9 (B), U5.9 (B), U6.9 (B), U7.9 (B), U8.9 (B), U9.9 (B), U10.9 (B), U11.9 (B), U12.9 (B), U13.9 (B), U14.9 (B)
unnamed: D1.2 (A), R5.2
unnamed: D2.2 (A), R6.2
unnamed: D3.2 (A), R7.2
unnamed: D4.2 (A), R8.2
unnamed: JP8.1 (A), R5.1, R6.1, R7.1, R8.1
unnamed: JP7.1 (A), U14.3 (Y)
SEL_LED_0: D1.1 (K), U14.1 (Y0)
SEL_LED_1: D2.1 (K), U14.5 (Y1)
SEL_LED_2: D3.1 (K), U14.2 (Y2)
SEL_LED_3: D4.1 (K), U14.4 (Y3)
